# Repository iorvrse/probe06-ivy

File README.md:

View this project on [CADLAB.io](https://cadlab.io/project/28579). 

# probe06-ivy

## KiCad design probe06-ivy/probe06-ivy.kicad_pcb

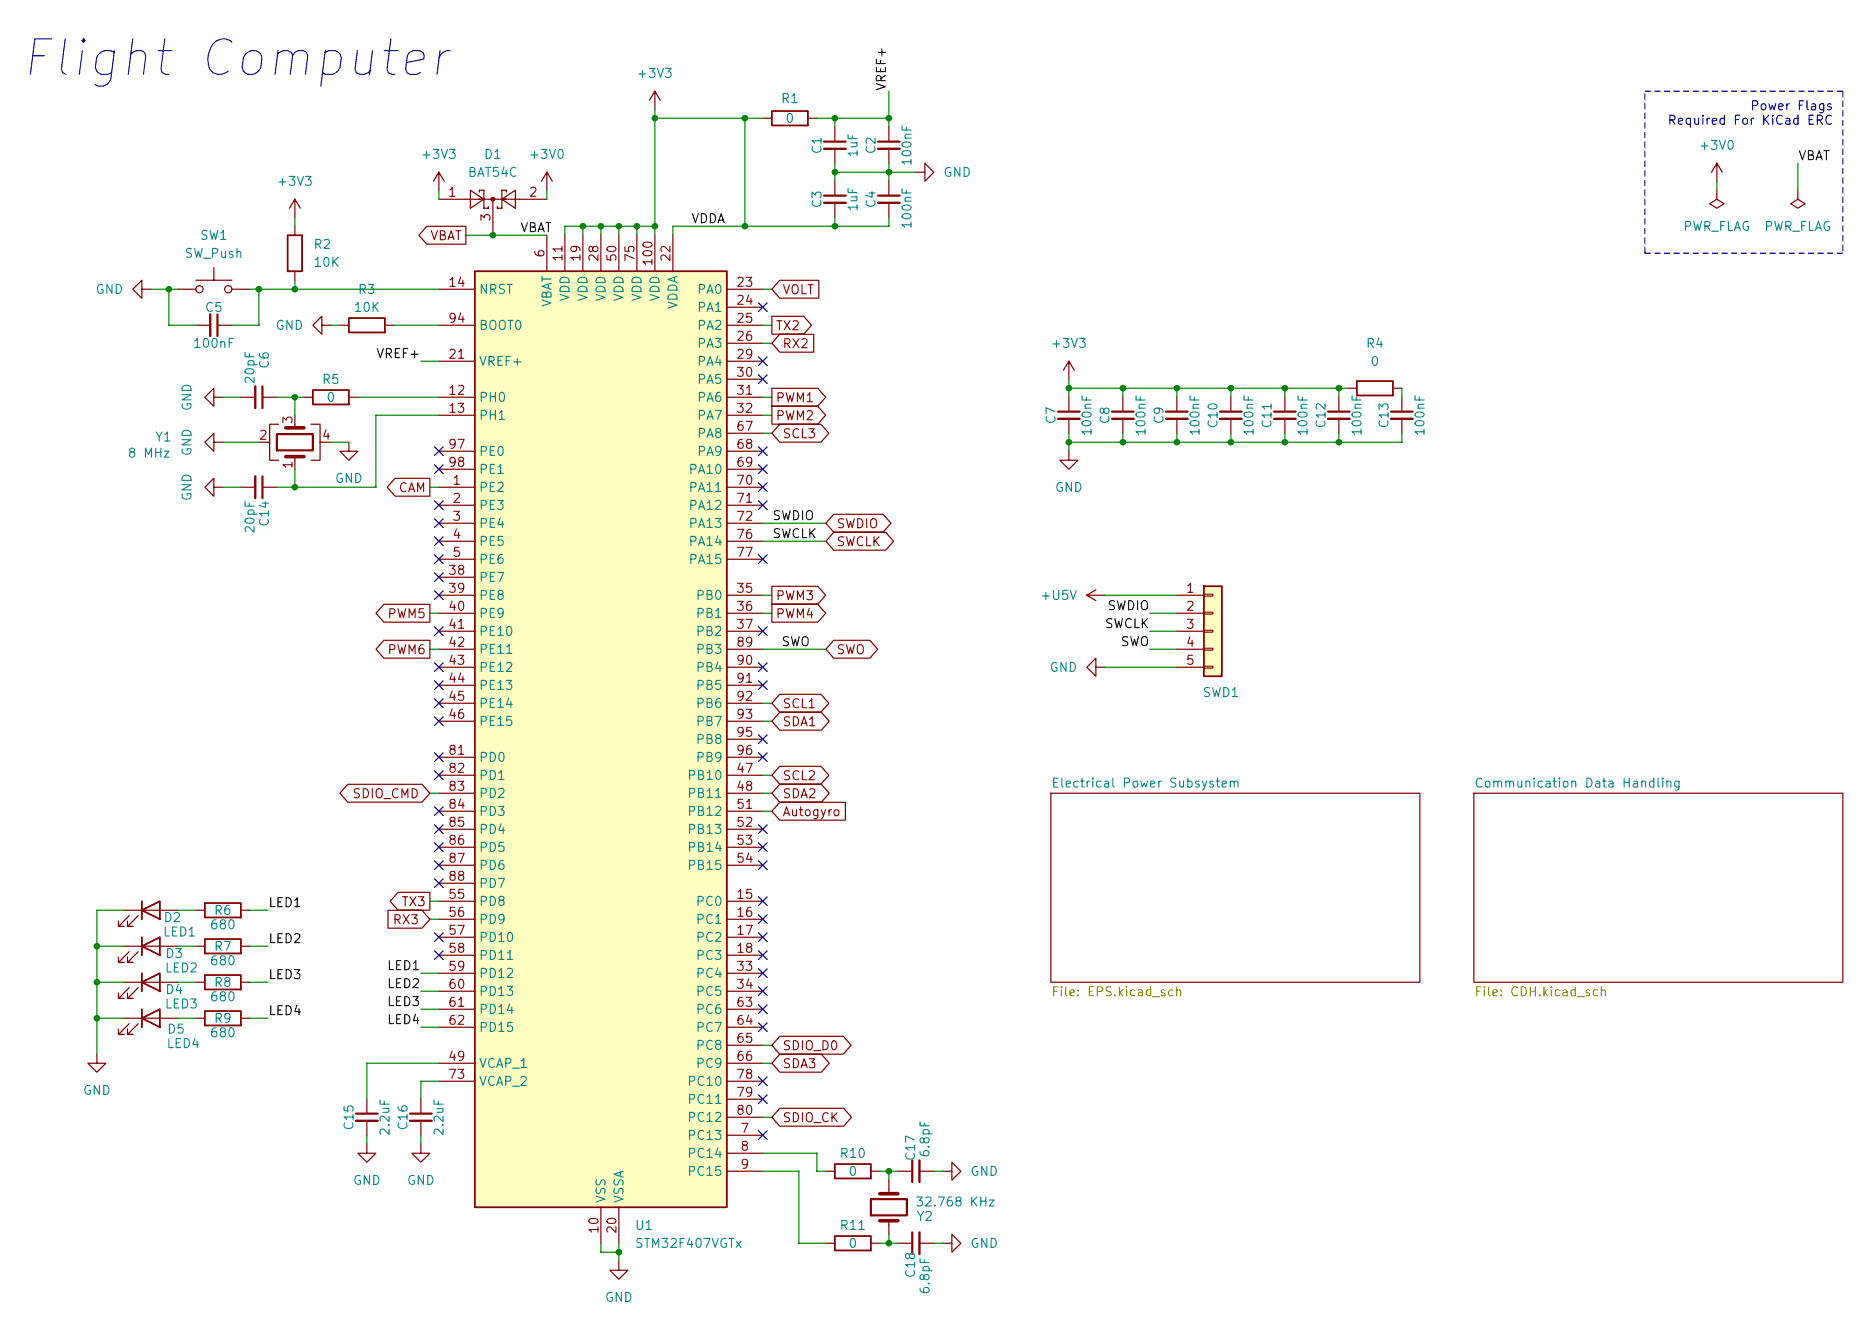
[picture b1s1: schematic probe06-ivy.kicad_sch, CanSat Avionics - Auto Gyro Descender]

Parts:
C1, C3: 1uF; C_0603_1608Metric
C2, C4, C5, C7, C8, C9, C10, C11, C12, C13: 100nF; C_0603_1608Metric
C6, C14: 20pF; C_0603_1608Metric
C15, C16: 2.2uF; C_0603_1608Metric
C17, C18: 6.8pF; C_0603_1608Metric
D1: BAT54C; SOT-23
D2: LED1; LED_0603_1608Metric
D3: LED2; LED_0603_1608Metric
D4: LED3; LED_0603_1608Metric
D5: LED4; LED_0603_1608Metric
R1, R4, R5, R10, R11: 0; R_0603_1608Metric
R2, R3: 10K; R_0603_1608Metric
R6, R7, R8, R9: 680; R_0603_1608Metric
SW1: SW_Push; SW_SPST_FSMSM
SWD1: JST_XH_B5B-XH-A_1x05_P2.50mm_Vertical
U1: STM32F407VGTx; LQFP-100_14x14mm_P0.5mm
Y1: 8 MHz; Crystal_SMD_3225-4Pin_3.2x2.5mm
Y2: 32.768 KHz; Crystal_C38-LF_D3.0mm_L8.0mm_Vertical

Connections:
+3V0: D1.2; also elsewhere on the board
+3V3: C3.2, C4.2, C7.1, C8.1, C9.1, C10.1, C11.1, C12.1, D1.1, R1.1, R2.1, R4.1, U1.11 (VDD), U1.19 (VDD), U1.22 (VDDA), U1.28 (VDD), U1.50 (VDD), U1.75 (VDD), U1.100 (VDD); also elsewhere on the board
+5V: SWD1.1; also elsewhere on the board
/LED1: R6.2, U1.59 (PD12)
/LED2: R7.2, U1.60 (PD13)
/LED3: R8.2, U1.61 (PD14)
/LED4: R9.2, U1.62 (PD15)
/VREF+: C1.1, C2.1, R1.2, U1.21 (VREF+)
Autogyro: U1.51 (PB12); also elsewhere on the board
CAM: U1.1 (PE2); also elsewhere on the board
GND: C1.2, C2.2, C3.1, C4.1, C5.2, C6.2, C7.2, C8.2, C9.2, C10.2, C11.2, C12.2, C13.2, C14.2, C15.2, C16.2, C17.2, C18.2, D2.1 (K), D3.1 (K), D4.1 (K), D5.1 (K), R3.1, SW1.1, SWD1.5, U1.10 (VSS), U1.20 (VSSA), U1.27 (VSS), U1.74 (VSS), U1.99 (VSS), Y1.2, Y1.4; also elsewhere on the board
unnamed: C6.1, R5.1, Y1.3
unnamed: C13.1, R4.2
unnamed: C17.1, R10.2, Y2.2
unnamed: C18.1, R11.2, Y2.1
unnamed: D2.2 (A), R6.1
unnamed: D3.2 (A), R7.1
unnamed: D4.2 (A), R8.1
unnamed: D5.2 (A), R9.1
unnamed: R3.2, U1.94 (BOOT0)
unnamed: C5.1, R2.2, SW1.2, U1.14 (NRST)
unnamed: R10.1, U1.8 (PC14)
unnamed: R11.1, U1.9 (PC15)
unnamed: R5.2, U1.12 (PH0)
unnamed: C14.1, U1.13 (PH1), Y1.1
unnamed: C15.1, U1.49 (VCAP_1)
unnamed: C16.1, U1.73 (VCAP_2)
PWM1: U1.31 (PA6); also elsewhere on the board
PWM2: U1.32 (PA7); also elsewhere on the board
PWM3: U1.35 (PB0); also elsewhere on the board
PWM4: U1.36 (PB1); also elsewhere on the board
PWM5: U1.40 (PE9); also elsewhere on the board
PWM6: U1.42 (PE11); also elsewhere on the board
RX2: U1.26 (PA3); also elsewhere on the board
RX3: U1.56 (PD9); also elsewhere on the board
SCL1: U1.92 (PB6); also elsewhere on the board
SCL2: U1.47 (PB10); also elsewhere on the board
SCL3: U1.67 (PA8); also elsewhere on the board
SDA1: U1.93 (PB7); also elsewhere on the board
SDA2: U1.48 (PB11); also elsewhere on the board
SDA3: U1.66 (PC9); also elsewhere on the board
SDIO_CK: U1.80 (PC12); also elsewhere on the board
SDIO_CMD: U1.83 (PD2); also elsewhere on the board
SDIO_D0: U1.65 (PC8); also elsewhere on the board
SWCLK: SWD1.3, U1.76 (PA14); also elsewhere on the board
SWDIO: SWD1.2, U1.72 (PA13); also elsewhere on the board
SWO: SWD1.4, U1.89 (PB3)
TX2: U1.25 (PA2); also elsewhere on the board
TX3: U1.55 (PD8); also elsewhere on the board
VBAT: D1.3, U1.6 (VBAT); also elsewhere on the board
VOLT: U1.23 (PA0); also elsewhere on the board

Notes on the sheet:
Power Flags Required For KiCad ERC
Flight Computer

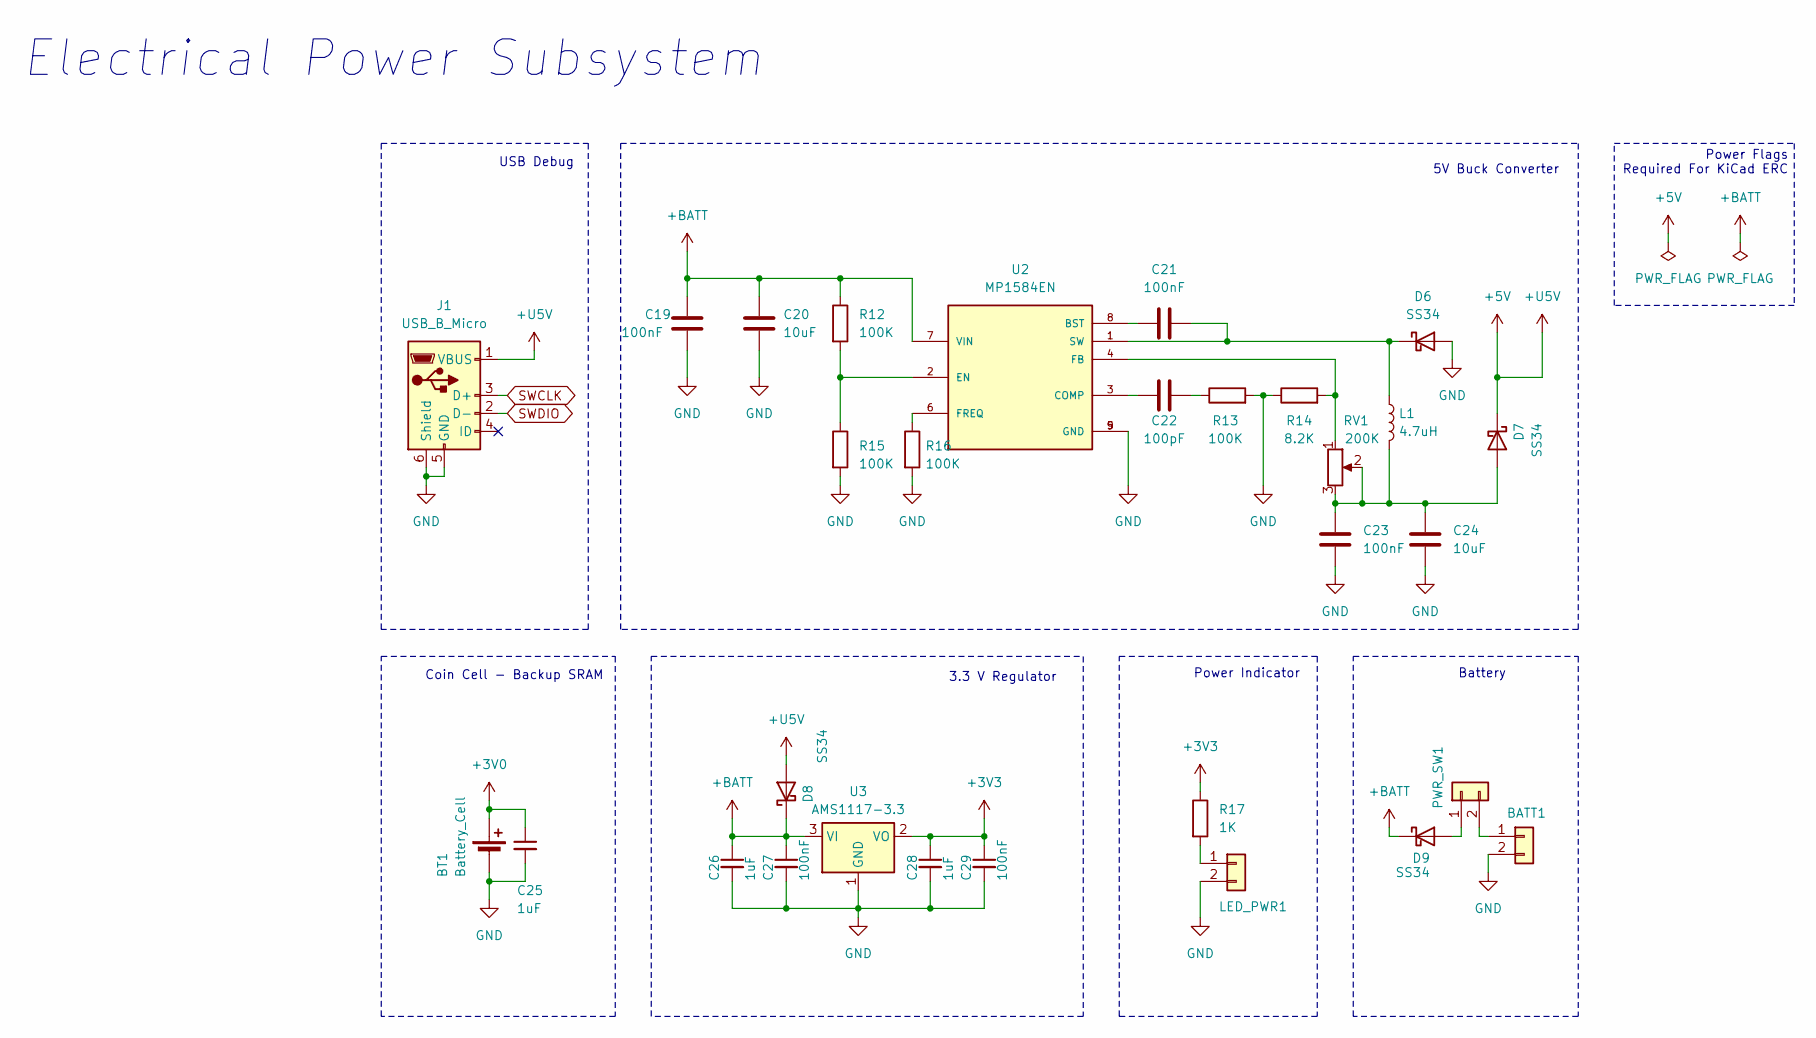
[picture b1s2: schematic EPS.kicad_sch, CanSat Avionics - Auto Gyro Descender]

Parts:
BATT1: xx; PinHeader_1x02_P2.54mm_Vertical
BT1: Battery_Cell; Battery_Holder_Coin_2032_BS-7
C19, C21, C23, C27, C29: 100nF; C_0603_1608Metric
C20, C24: 10uF; C_1206_3216Metric
C22: 100pF; C_0603_1608Metric
C25, C26, C28: 1uF; C_0603_1608Metric
D6, D7, D8, D9: SS34; D_SMA
J1: USB_B_Micro; USB_Micro-B_Amphenol_10104110_Horizontal
L1: 4.7uH; L_6.3x6.3_H3
LED_PWR1: xx; JST_XH_B2B-XH-A_1x02_P2.50mm_Vertical
PWR_SW1: xx; JST_XH_B2B-XH-A_1x02_P2.50mm_Vertical
R12, R13, R15, R16: 100K; R_0603_1608Metric
R14: 8.2K; R_0603_1608Metric
R17: 1K; R_0603_1608Metric
RV1: 200K; TRIM_TC33X-2-103E
U2: MP1584EN; SOIC127P600X170-9N
U3: AMS1117-3.3; SOT-223-3_TabPin2

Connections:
+3V0: BT1.1 (+), C25.1; also elsewhere on the board
+3V3: C28.1, C29.1, R17.1, U3.2 (VO); also elsewhere on the board
+5V: D7.1 (K), D8.2 (A), J1.1 (VBUS); also elsewhere on the board
+BATT: C19.1, C20.1, C26.1, C27.1, D8.1 (K), D9.1 (K), R12.1, U2.7 (VIN), U3.3 (VI); also elsewhere on the board
GND: BATT1.2, BT1.2 (-), C19.2, C20.2, C23.2, C24.2, C25.2, C26.2, C27.2, C28.2, C29.2, D6.2 (A), J1.5 (GND), J1.6 (Shield), LED_PWR1.2, R13.2, R14.1, R15.2, R16.2, U2.5 (GND), U2.9 (GND), U3.1 (GND); also elsewhere on the board
unnamed: BATT1.1, PWR_SW1.2
unnamed: C22.2, R13.1
unnamed: C21.2, D6.1 (K), L1.1, U2.1 (SW)
unnamed: C23.1, C24.1, D7.2 (A), L1.2, RV1.2, RV1.3
unnamed: D9.2 (A), PWR_SW1.1
unnamed: LED_PWR1.1, R17.2
unnamed: C21.1, U2.8 (BST)
unnamed: C22.1, U2.3 (COMP)
unnamed: R12.2, R15.1, U2.2 (EN)
unnamed: R14.2, RV1.1, U2.4 (FB)
unnamed: R16.1, U2.6 (FREQ)
SWCLK: J1.3 (D+); also elsewhere on the board
SWDIO: J1.2 (D-); also elsewhere on the board

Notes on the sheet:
Power Flags Required For KiCad ERC
3.3 V Regulator
Coin Cell - Backup SRAM
Electrical Power Subsystem
USB Debug
Battery
5V Buck Converter
Power Indicator

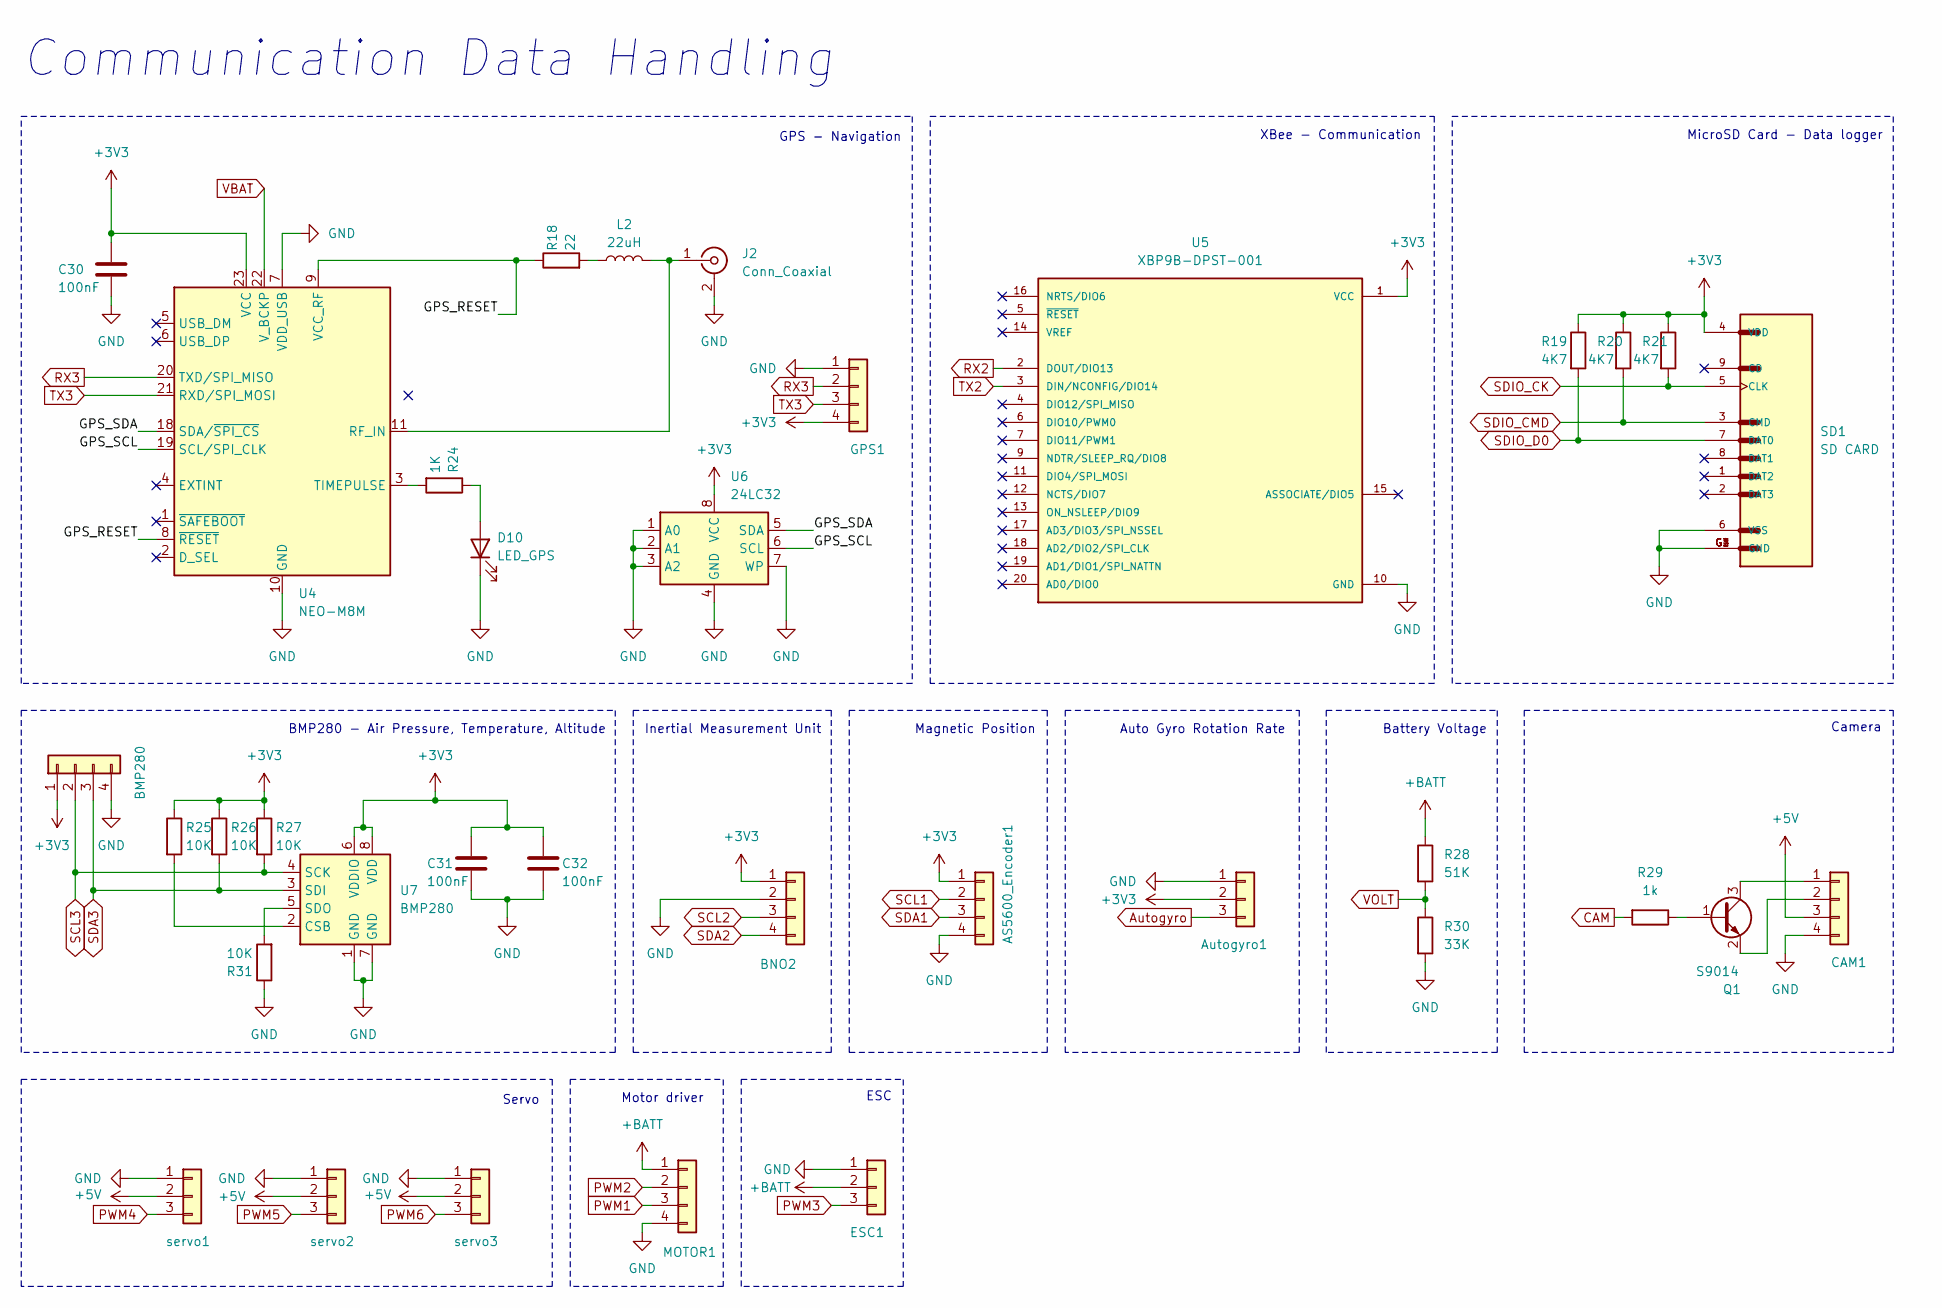
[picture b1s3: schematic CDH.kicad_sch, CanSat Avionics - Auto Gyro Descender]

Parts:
AS5600_Encoder1: xx; JST_XH_B4B-XH-A_1x04_P2.50mm_Vertical
Autogyro1: xx; JST_XH_B3B-XH-A_1x03_P2.50mm_Vertical
BMP280: xx; PinHeader_1x04_P2.54mm_Vertical
BNO2: xx; PinHeader_1x04_P2.54mm_Vertical
C30, C31, C32: 100nF; C_0603_1608Metric
CAM1: xx; JST_XH_B4B-XH-A_1x04_P2.50mm_Vertical
D10: LED_GPS; LED_0603_1608Metric
ESC1: xx; JST_XH_B3B-XH-A_1x03_P2.50mm_Vertical
GPS1: xx; PinHeader_1x04_P2.54mm_Vertical
J2: Conn_Coaxial; U.FL_Hirose_U.FL-R-SMT-1_Vertical
L2: 22uH; L_0805_2012Metric
MOTOR1: xx; JST_XH_B4B-XH-A_1x04_P2.50mm_Vertical
Q1: S9014; SOT-23
R18: 22; R_0603_1608Metric
R19, R20, R21: 4K7; R_0603_1608Metric
R24: 1K; R_0603_1608Metric
R25, R26, R27, R31: 10K; R_0603_1608Metric
R28: 51K; R_0603_1608Metric
R29: 1k; R_0603_1608Metric
R30: 33K; R_0603_1608Metric
SD1: SD CARD; SUNTECH_ST-TF-003A
U4: NEO-M8M; ublox_NEO
U5: XBP9B-DPST-001; DIP2200W51P200L3294H279Q20P
U6: 24LC32; TSSOP-8_4.4x3mm_P0.65mm
U7: BMP280; Bosch_LGA-8_2x2.5mm_P0.65mm_ClockwisePinNumbering
servo1, servo2, servo3: xx; JST_XH_B3B-XH-A_1x03_P2.50mm_Vertical

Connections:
+3V3: AS5600_Encoder1.1, Autogyro1.2, BMP280.1, BNO2.1, C30.1, C31.1, C32.1, GPS1.4, R19.1, R20.1, R21.1, R25.1, R26.1, R27.1, SD1.4 (VDD), U4.23 (VCC), U5.1 (VCC), U6.8 (VCC), U7.6 (VDDIO), U7.8 (VDD); also elsewhere on the board
+5V: CAM1.3, servo1.2, servo2.2, servo3.2; also elsewhere on the board
+BATT: ESC1.2, MOTOR1.1, R28.1; also elsewhere on the board
/Communication Data Handling/GPS_RESET: R18.1, U4.8 (~RESET), U4.9 (VCC_RF)
/Communication Data Handling/GPS_SCL: U4.19 (SCL/SPI_CLK), U6.6 (SCL)
/Communication Data Handling/GPS_SDA: U4.18 (SDA/~SPI_CS), U6.5 (SDA)
Autogyro: Autogyro1.3; also elsewhere on the board
CAM: R29.2; also elsewhere on the board
GND: AS5600_Encoder1.4, Autogyro1.1, BMP280.4, BNO2.2, C30.2, C31.2, C32.2, CAM1.4, D10.1 (K), ESC1.1, GPS1.1, J2.2 (Ext), MOTOR1.4, R30.2, R31.1, SD1.6 (VSS), SD1.G1 (GND), SD1.G2 (GND), SD1.G3 (GND), SD1.G4 (GND), U4.7 (VDD_USB), U4.10 (GND), U4.12 (GND), U4.13 (GND), U4.24 (GND), U5.10 (GND), U6.1 (A0), U6.2 (A1), U6.3 (A2), U6.4 (GND), U6.7 (WP), U7.1 (GND), U7.7 (GND), servo1.1, servo2.1, servo3.1; also elsewhere on the board
unnamed: CAM1.1, Q1.3 (C)
unnamed: CAM1.2, Q1.2 (E)
unnamed: D10.2 (A), R24.1
unnamed: J2.1 (In), L2.2, U4.11 (RF_IN)
unnamed: L2.1, R18.2
unnamed: Q1.1 (B), R29.1
unnamed: R24.2, U4.3 (TIMEPULSE)
unnamed: R25.2, U7.2 (CSB)
unnamed: R31.2, U7.5 (SDO)
PWM1: MOTOR1.3; also elsewhere on the board
PWM2: MOTOR1.2; also elsewhere on the board
PWM3: ESC1.3; also elsewhere on the board
PWM4: servo1.3; also elsewhere on the board
PWM5: servo2.3; also elsewhere on the board
PWM6: servo3.3; also elsewhere on the board
RX2: U5.2 (DOUT/DIO13); also elsewhere on the board
RX3: GPS1.2, U4.20 (TXD/SPI_MISO); also elsewhere on the board
SCL1: AS5600_Encoder1.2; also elsewhere on the board
SCL2: BNO2.3; also elsewhere on the board
SCL3: BMP280.2, R27.2, U7.4 (SCK); also elsewhere on the board
SDA1: AS5600_Encoder1.3; also elsewhere on the board
SDA2: BNO2.4; also elsewhere on the board
SDA3: BMP280.3, R26.2, U7.3 (SDI); also elsewhere on the board
SDIO_CK: R21.2, SD1.5 (CLK); also elsewhere on the board
SDIO_CMD: R20.2, SD1.3 (CMD); also elsewhere on the board
SDIO_D0: R19.2, SD1.7 (DAT0); also elsewhere on the board
TX2: U5.3 (DIN/NCONFIG/DIO14); also elsewhere on the board
TX3: GPS1.3, U4.21 (RXD/SPI_MOSI); also elsewhere on the board
VBAT: U4.22 (V_BCKP); also elsewhere on the board
VOLT: R28.2, R30.1; also elsewhere on the board

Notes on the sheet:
Servo
ESC
MicroSD Card - Data logger
Auto Gyro Rotation Rate
Magnetic Position
Inertial Measurement Unit
Camera
BMP280 - Air Pressure, Temperature, Altitude
Motor driver
Battery Voltage
Communication Data Handling
GPS - Navigation
XBee - Communication

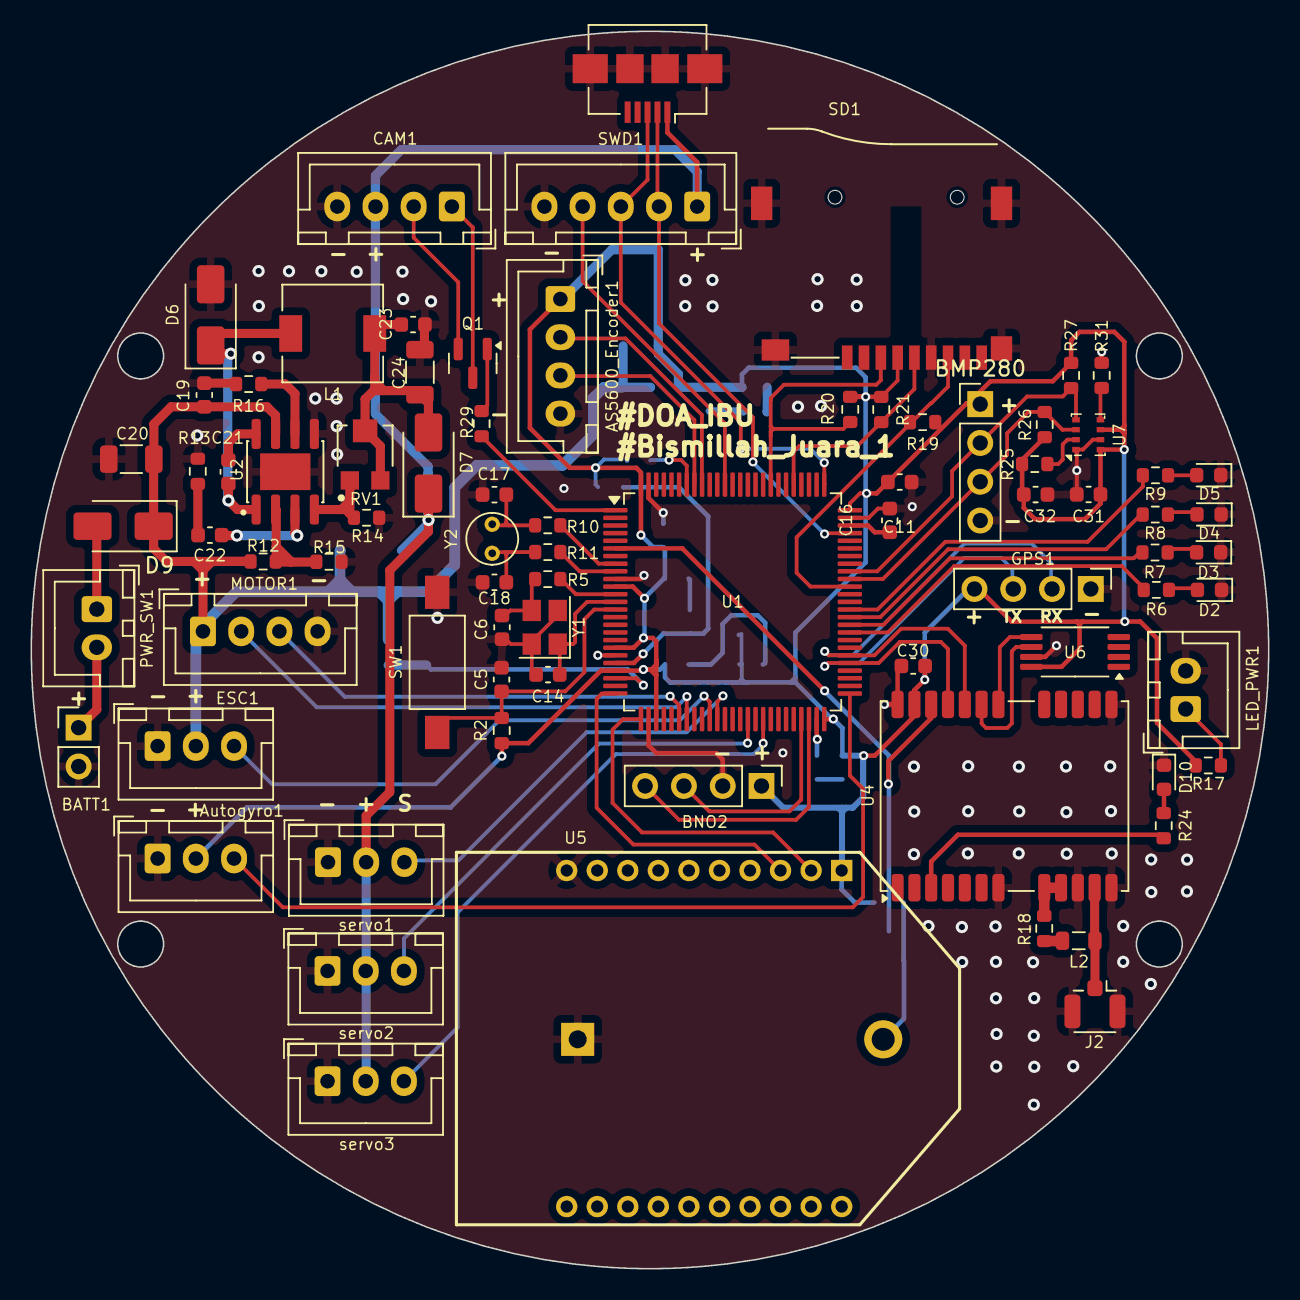
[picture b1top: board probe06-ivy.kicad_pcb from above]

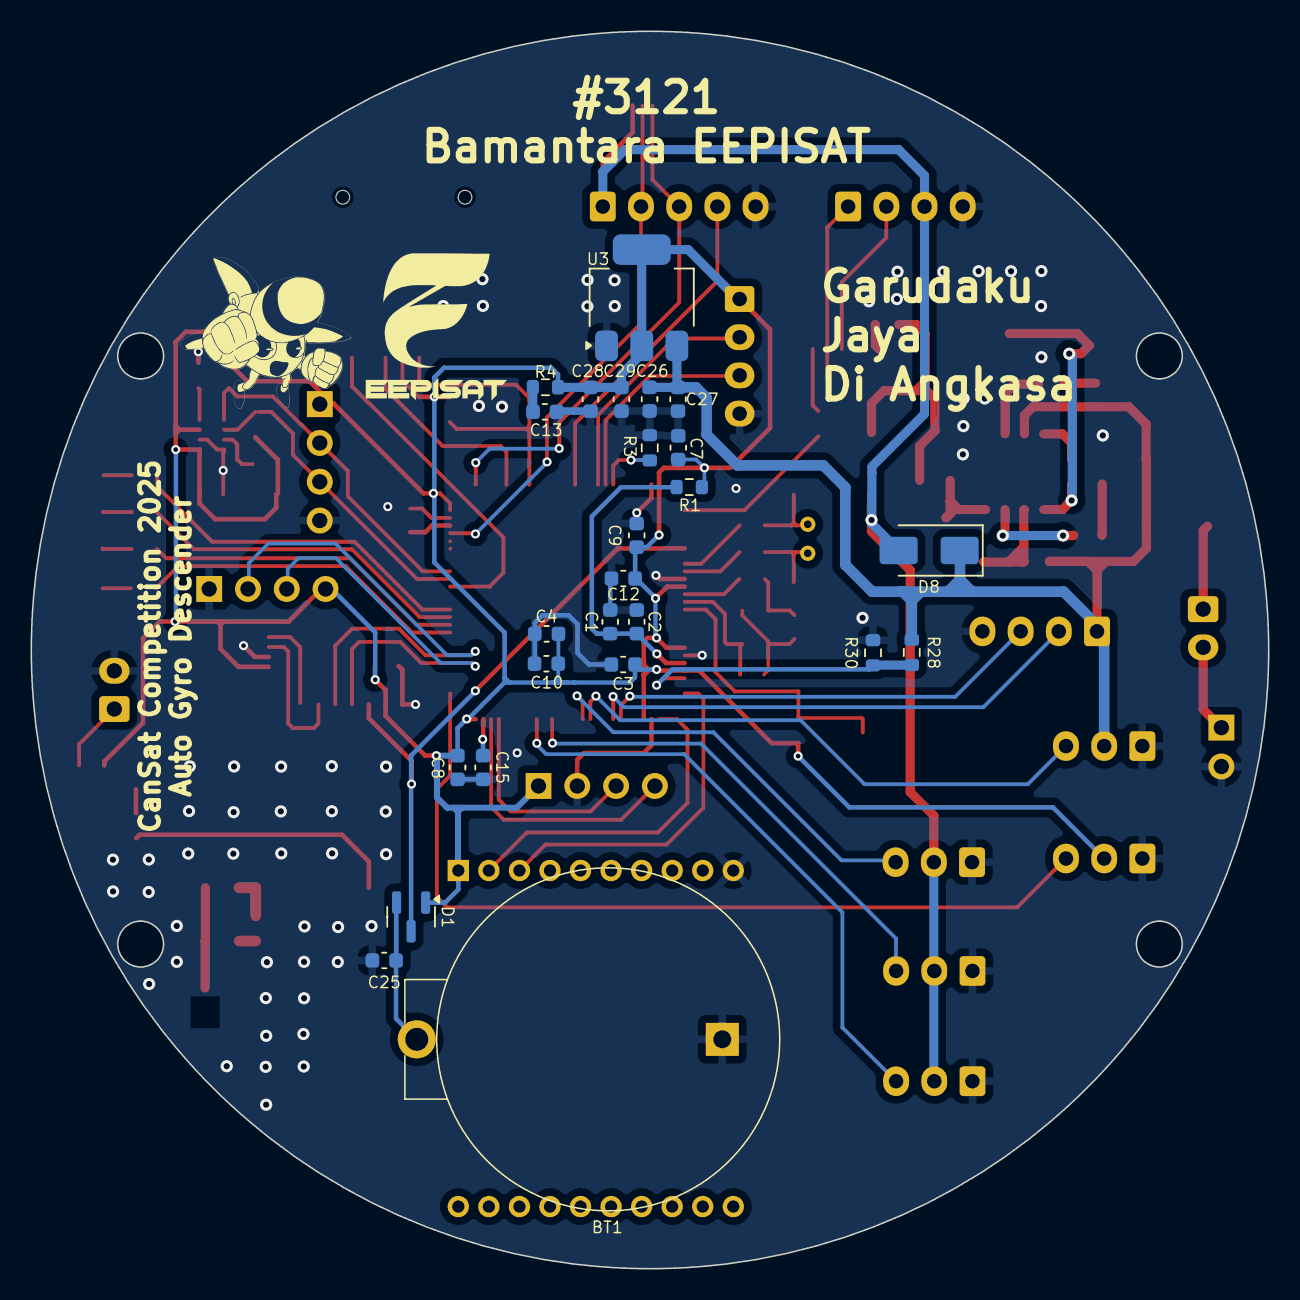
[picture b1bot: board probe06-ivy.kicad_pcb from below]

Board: 2 copper layers, 81.0 x 81.0 mm, 104 parts (25 on the bottom side), 75 nets.

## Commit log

2024-10-21 EPS design for 1 battery
2024-10-21 remove deprecated schematics
2024-10-21 Backlink to CADLAB.io has been added.
2024-11-22 Routing Layout - add footprint to all components - pcb shape and dimension - component placement
2024-11-22 route crystal and some bypass cap
2024-11-23 Routing (2) - make the pcb edge cuts to suit mechanic requirements - route some components (power, usb debug, gps) progress 50%
2024-11-25 Routing (3) Signal routing mostly done with something that needs TODO next: - Correction for power signals - Tidy up component silkscreen - Add team name and tagline
2024-11-26 Routing (3)
2024-11-26 order id placement
2025-01-13 Some revision to meet pcb service requirements - Change via hole diameter - Via and component placement - etc
2025-02-08 rev 1.2
2025-02-19 rev 1.2.1 add additional pin
2025-02-19 minor changes
2025-02-21 mboh
